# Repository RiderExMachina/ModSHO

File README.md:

# ModSHO

PCB for the [ModXO Xbox hardmod by Shalx](https://github.com/shalxmva/modxo). Designed for manufacturability and minor customizability. See [BOM.md](BOM.md) for the Bill of Materials.

The build takes heavy inspiration from [m4x10187's Adapter](https://github.com/m4x10187/Modxo_RP2040_Zero_Adapter).

The board is 40mm x 30mm, as seen below.

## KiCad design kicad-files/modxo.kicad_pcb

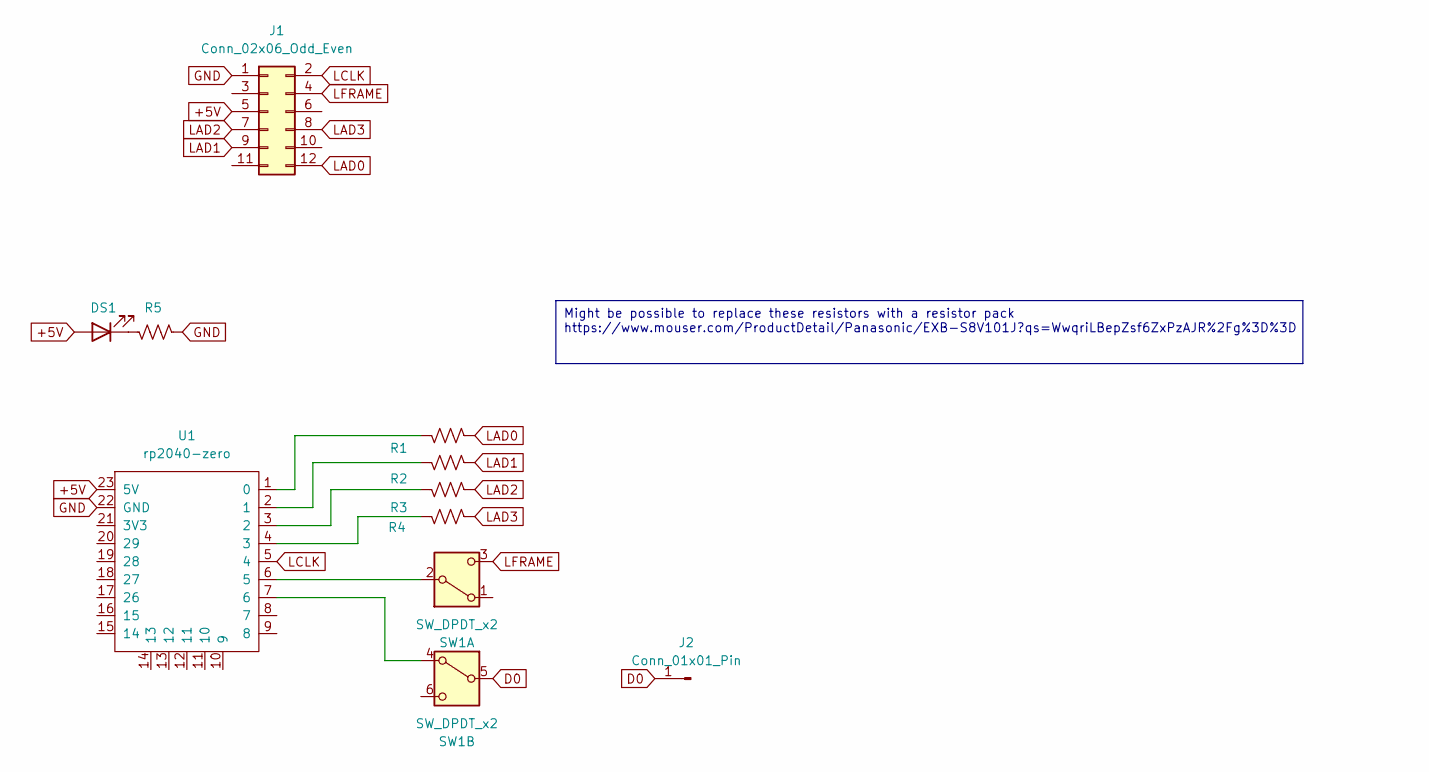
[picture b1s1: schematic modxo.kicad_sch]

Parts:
DS1: LED; LED_1210_3225Metric_Pad1.42x2.65mm_HandSolder
J1: Conn_02x06_Odd_Even; PinHeader_2x06_P2.54mm_Vertical
J2: Conn_01x01_Pin; SolderWirePad_1x01_SMD_1x2mm
R1, R2, R3, R4, R5: R_US; R_0805_2012Metric_Pad1.20x1.40mm_HandSolder
SW1: SW_DPDT_x2; SW_DPDT_CK_JS202011JCQN
U1: rp2040-zero; rp2040-zero-smd

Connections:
+5V: DS1.2 (A), J1.5, U1.23 (5V)
D0: J2.1, SW1.5 (B)
GND: J1.1, R5.2, U1.22 (GND)
LAD0: J1.12, R1.2
LAD1: J1.9, R2.2
LAD2: J1.7, R3.2
LAD3: J1.8, R4.2
LCLK: J1.2, U1.5 (4)
LFRAME: J1.4, SW1.3 (C)
unnamed: DS1.1 (K), R5.1
unnamed: SW1.2 (B), U1.6 (5)
unnamed: SW1.4 (A), U1.7 (6)
unnamed: R1.1, U1.1 (0)
unnamed: R2.1, U1.2 (1)
unnamed: R3.1, U1.3 (2)
unnamed: R4.1, U1.4 (3)

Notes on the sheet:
Might be possible to replace these resistors with a resistor pack https://www.mouser.com/ProductDetail/Panasonic/EXB-S8V101J?qs=WwqriLBepZsf6ZxPzAJR%2Fg%3D%3D

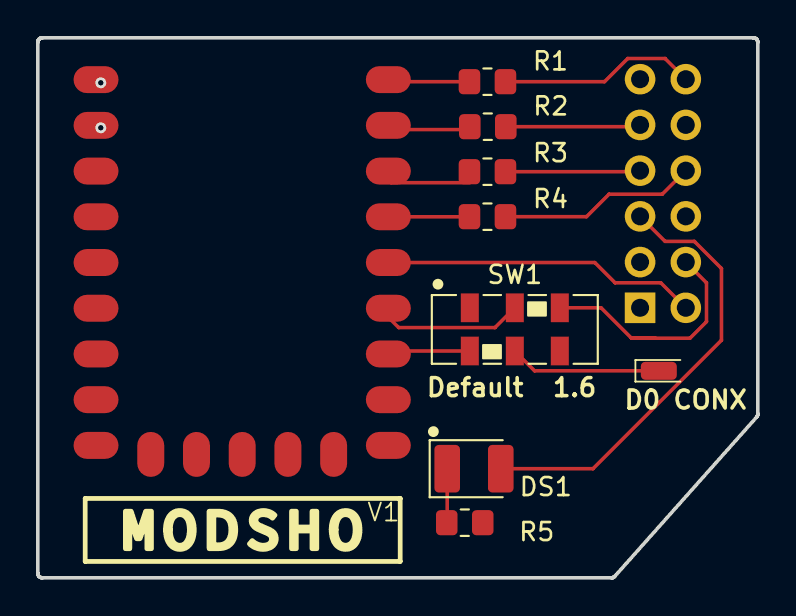
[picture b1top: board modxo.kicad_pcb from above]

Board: 2 copper layers, 40.0 x 30.0 mm, 10 parts (1 on the bottom side), 16 nets.

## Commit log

2024-07-05 Basic V1 with BOM
2024-07-05 Minor usability improvements
2024-07-05 Add photo of board
2024-07-07 Update README.md
    Fix a hyperlink and add the image of the board as a visual
